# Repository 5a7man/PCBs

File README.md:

# PCBs
## Power Supply

## AVR Based Datalogger

## LED Matrix

## Amplitude Modulation and Demodulation

## Class D Amplifier

## Wireless Power Transmission

## Bluetooth Controlled Vehicle

## Metal Detector

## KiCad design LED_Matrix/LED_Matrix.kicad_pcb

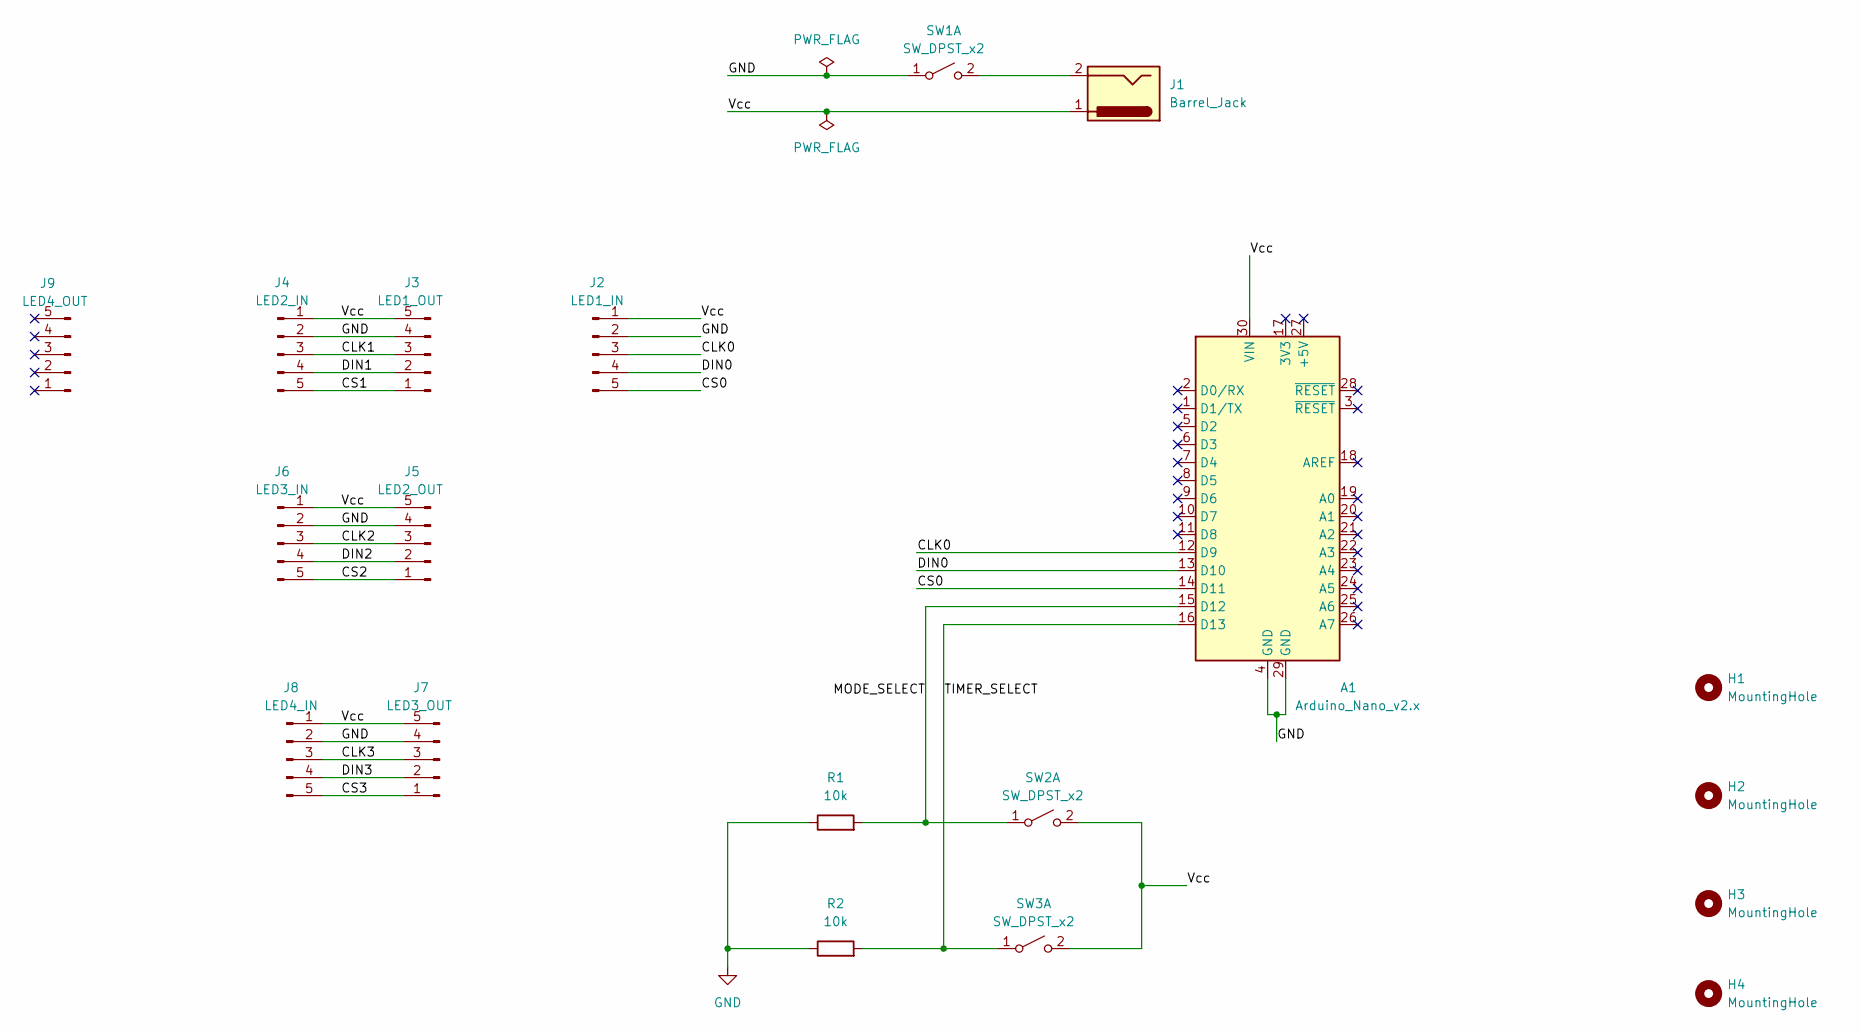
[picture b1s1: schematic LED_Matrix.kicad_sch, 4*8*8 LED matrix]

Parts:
A1: Arduino_Nano_v2.x; Arduino_Nano_WithMountingHoles
H1, H2, H3, H4: MountingHole; MountingHole_2.5mm
J1: Barrel_Jack; BarrelJack_SwitchcraftConxall_RAPC10U_Horizontal
J2: LED1_IN; PinSocket_1x05_P2.54mm_Vertical
J3: LED1_OUT; PinSocket_1x05_P2.54mm_Vertical
J4: LED2_IN; PinSocket_1x05_P2.54mm_Vertical
J5: LED2_OUT; PinSocket_1x05_P2.54mm_Vertical
J6: LED3_IN; PinSocket_1x05_P2.54mm_Vertical
J7: LED3_OUT; PinSocket_1x05_P2.54mm_Vertical
J8: LED4_IN; PinSocket_1x05_P2.54mm_Vertical
J9: LED4_OUT; PinSocket_1x05_P2.54mm_Vertical
R1, R2: 10k; R_Axial_DIN0207_L6.3mm_D2.5mm_P10.16mm_Horizontal
SW1: SW_DPST_x2; SW_DIP_SPSTx02_Slide_6.7x6.64mm_W7.62mm_P2.54mm_LowProfile
SW2, SW3: SW_DPST_x2; Push_E-Switch_KS01Q01

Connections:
/CLK0: A1.12 (D9), J2.3
/CLK1: J3.3, J4.3
/CLK2: J5.3, J6.3
/CLK3: J7.3, J8.3
/CS0: A1.14 (D11), J2.5
/CS1: J3.1, J4.5
/CS2: J5.1, J6.5
/CS3: J7.1, J8.5
/DIN0: A1.13 (D10), J2.4
/DIN1: J3.2, J4.4
/DIN2: J5.2, J6.4
/DIN3: J7.2, J8.4
/MODE_SELECT: A1.15 (D12), R1.2, SW2.1 (A)
/TIMER_SELECT: A1.16 (D13), R2.2, SW3.1 (A)
/Vcc: A1.30 (VIN), J1.1, J2.1, J3.5, J4.1, J5.5, J6.1, J7.5, J8.1, SW2.2 (B), SW3.2 (B)
GND: A1.4 (GND), A1.29 (GND), J2.2, J3.4, J4.2, J5.4, J6.2, J7.4, J8.2, R1.1, R2.1, SW1.1 (A)
unnamed: J1.2, SW1.2 (B)

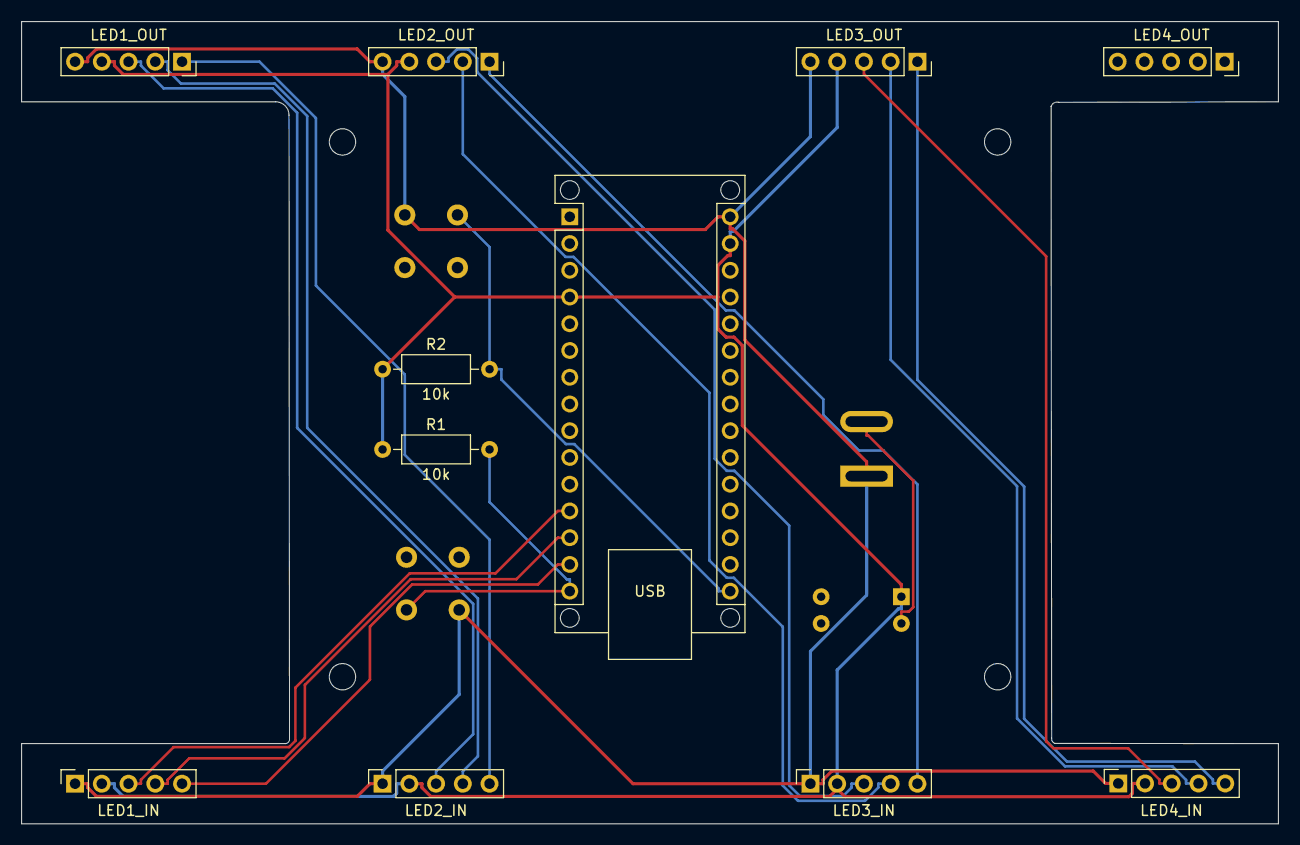
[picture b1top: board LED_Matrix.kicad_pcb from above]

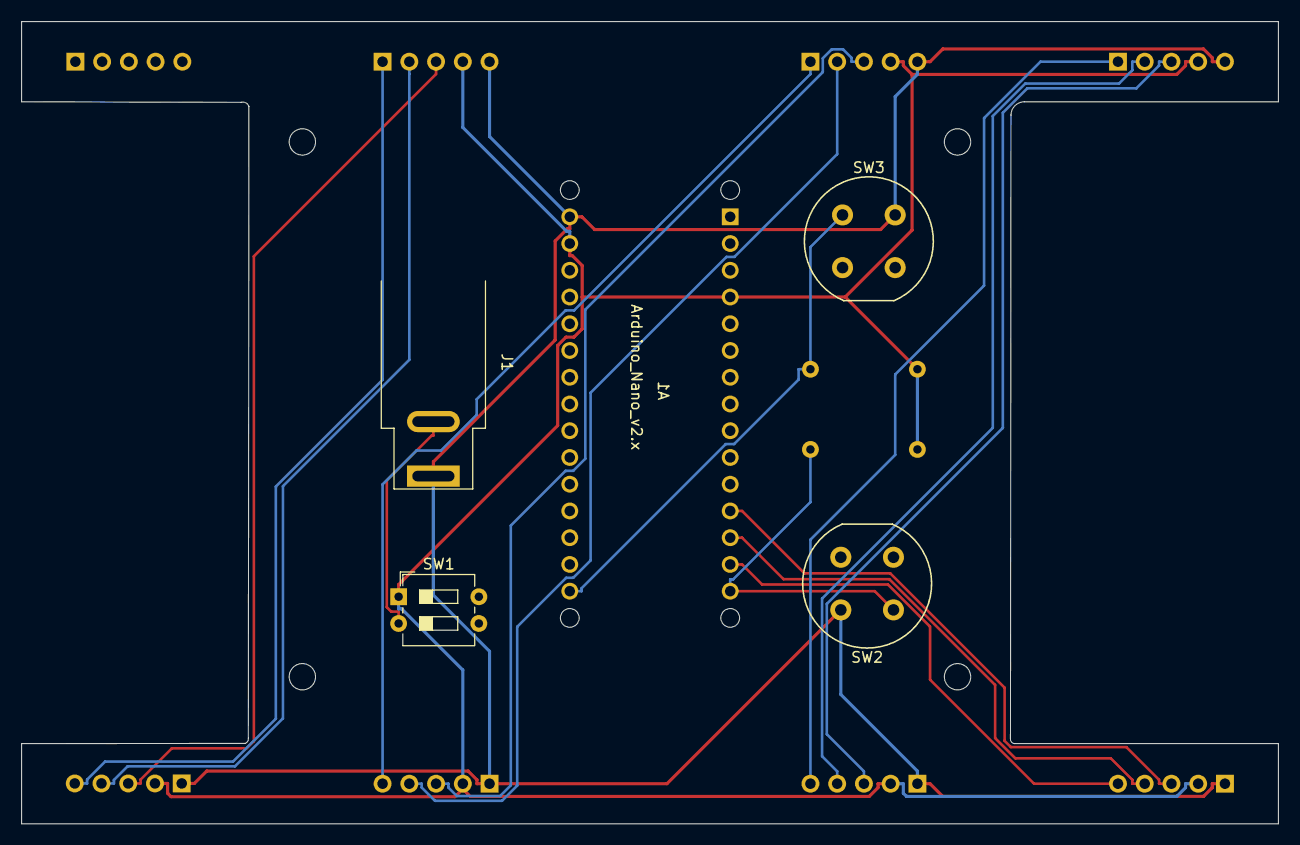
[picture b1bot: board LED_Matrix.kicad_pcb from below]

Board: 2 copper layers, 119.4 x 76.2 mm, 19 parts (4 on the bottom side), 17 nets.

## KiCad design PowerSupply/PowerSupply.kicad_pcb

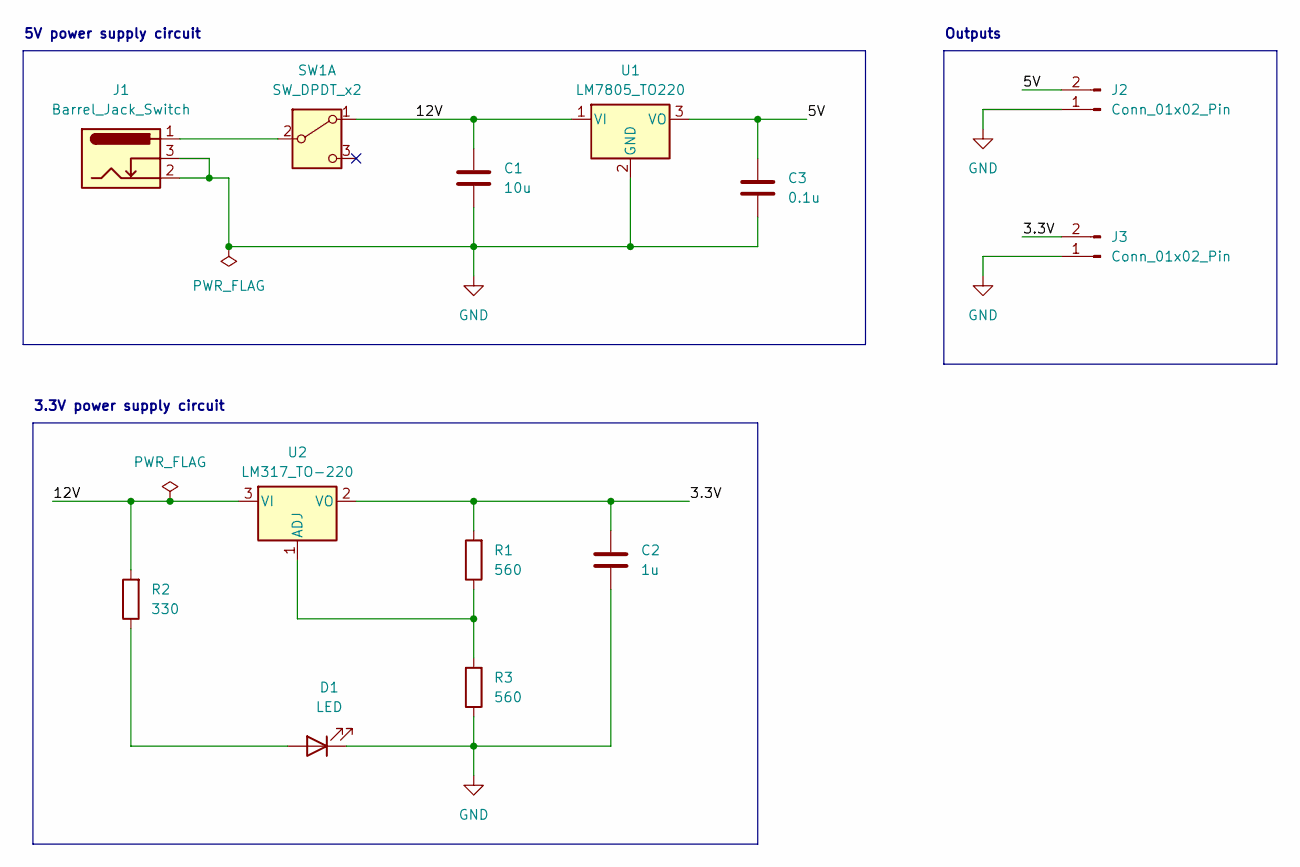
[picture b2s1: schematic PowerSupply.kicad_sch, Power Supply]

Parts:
C1: 10u; C_Disc_D3.0mm_W1.6mm_P2.50mm
C2: 1u; C_Disc_D3.0mm_W1.6mm_P2.50mm
C3: 0.1u; C_Disc_D3.0mm_W1.6mm_P2.50mm
D1: LED; LED_D5.0mm
J1: Barrel_Jack_Switch; BarrelJack_Horizontal
J2, J3: Conn_01x02_Pin; PinHeader_1x02_P2.54mm_Vertical
R1, R3: 560; R_Axial_DIN0204_L3.6mm_D1.6mm_P7.62mm_Horizontal
R2: 330; R_Axial_DIN0204_L3.6mm_D1.6mm_P7.62mm_Horizontal
SW1: SW_DPDT_x2; SW_CuK_JS202011CQN_DPDT_Straight
U1: LM7805_TO220; TO-220-3_Vertical
U2: LM317_TO-220; TO-220-3_Vertical

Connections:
/3.3V: C2.1, J3.2, R1.2, U2.2 (VO)
/5V: C3.1, J2.2, U1.3 (VO)
/12V: C1.1, R2.2, SW1.1 (A), U1.1 (VI), U2.3 (VI)
GND: C1.2, C2.2, C3.2, D1.1 (K), J1.2, J1.3, J2.1, J3.1, R3.1, U1.2 (GND)
unnamed: D1.2 (A), R2.1
unnamed: J1.1, SW1.2 (B)
unnamed: R1.1, R3.2, U2.1 (ADJ)

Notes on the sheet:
Outputs
5V power supply circuit
3.3V power supply circuit

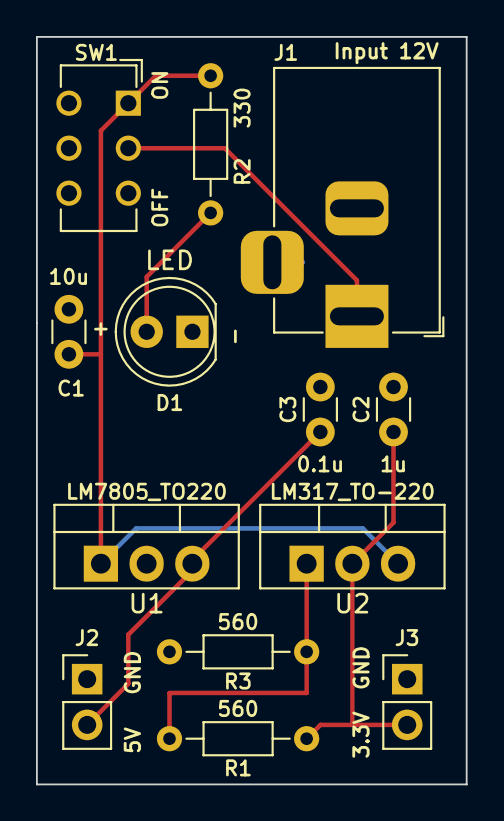
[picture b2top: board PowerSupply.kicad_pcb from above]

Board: 2 copper layers, 23.9 x 41.5 mm, 13 parts (0 on the bottom side), 7 nets.

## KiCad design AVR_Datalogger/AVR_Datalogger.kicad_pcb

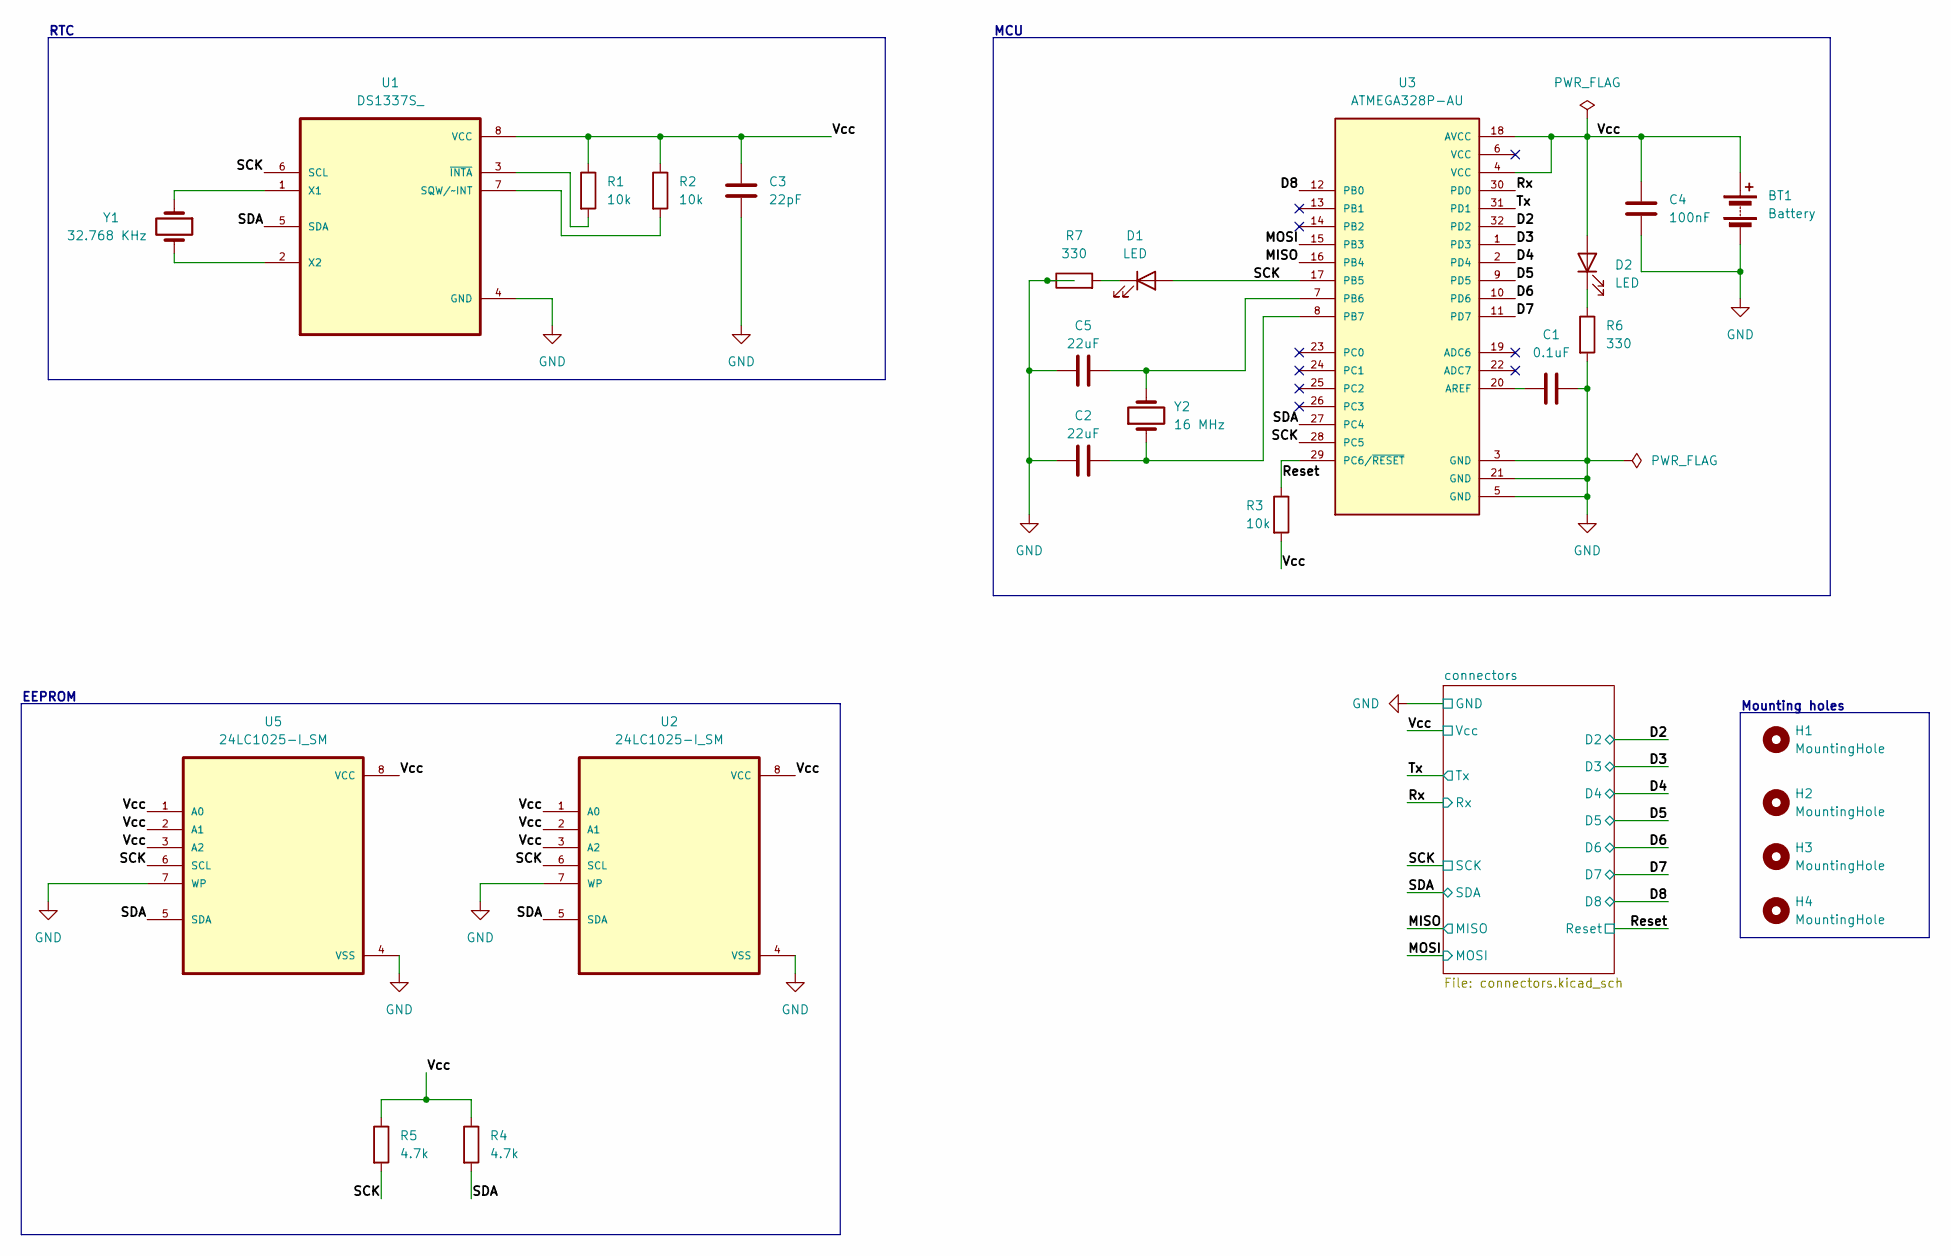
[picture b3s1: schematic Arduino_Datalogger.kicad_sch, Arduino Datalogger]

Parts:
BT1: Battery; PinHeader_1x02_P2.54mm_Vertical
C1: 0.1uF; C_0805_2012Metric
C2, C5: 22uF; C_0805_2012Metric
C3: 22pF; C_0805_2012Metric
C4: 100nF; C_0805_2012Metric
D1, D2: LED; LED_0805_2012Metric
H1, H2, H3, H4: MountingHole; MountingHole_2.1mm
R1, R2, R3: 10k; R_0805_2012Metric
R4, R5: 4.7k; R_0805_2012Metric
R6, R7: 330; R_0805_2012Metric
U1: DS1337S_; SOIC127P600X175-8N
U2, U5: 24LC1025-I_SM; SOIC127P794X202-8N
U3: ATMEGA328P-AU; QFP80P900X900X120-32N; PARTREV 8271A
Y1: 32.768 KHz; Crystal_SMD_5032-2Pin_5.0x3.2mm_HandSoldering
Y2: 16 MHz; Crystal_SMD_5032-2Pin_5.0x3.2mm_HandSoldering

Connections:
/D2: U3.32 (PD2); also elsewhere on the board
/D3: U3.1 (PD3); also elsewhere on the board
/D4: U3.2 (PD4); also elsewhere on the board
/D5: U3.9 (PD5); also elsewhere on the board
/D6: U3.10 (PD6); also elsewhere on the board
/D7: U3.11 (PD7); also elsewhere on the board
/D8: U3.12 (PB0); also elsewhere on the board
/MISO: U3.16 (PB4); also elsewhere on the board
/MOSI: U3.15 (PB3); also elsewhere on the board
/Reset: R3.1, U3.29 (PC6/~RESET); also elsewhere on the board
/Rx: U3.30 (PD0); also elsewhere on the board
/SCK: D1.2 (A), R5.2, U1.6 (SCL), U2.6 (SCL), U3.17 (PB5), U3.28 (PC5), U5.6 (SCL); also elsewhere on the board
/SDA: R4.2, U1.5 (SDA), U2.5 (SDA), U3.27 (PC4), U5.5 (SDA); also elsewhere on the board
/Tx: U3.31 (PD1); also elsewhere on the board
/Vcc: BT1.1 (+), C3.1, C4.1, D2.2 (A), R1.1, R2.1, R3.2, R4.1, R5.1, U1.8 (VCC), U2.1 (A0), U2.2 (A1), U2.3 (A2), U2.8 (VCC), U3.4 (VCC), U3.18 (AVCC), U5.1 (A0), U5.2 (A1), U5.3 (A2), U5.8 (VCC); also elsewhere on the board
GND: BT1.2 (-), C1.2, C2.1, C3.2, C4.2, C5.1, R6.2, R7.1, U1.4 (GND), U2.4 (VSS), U2.7 (WP), U3.3 (GND), U3.5 (GND), U3.21 (GND), U5.4 (VSS), U5.7 (WP); also elsewhere on the board
unnamed: D1.1 (K), R7.2
unnamed: D2.1 (K), R6.1
unnamed: R2.2, U1.7 (SQW/~INT)
unnamed: U1.1 (X1), Y1.1
unnamed: U1.2 (X2), Y1.2
unnamed: R1.2, U1.3 (~INTA)
unnamed: C1.1, U3.20 (AREF)
unnamed: C5.2, U3.7 (PB6), Y2.2
unnamed: C2.2, U3.8 (PB7), Y2.1

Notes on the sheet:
MCU
EEPROM
RTC
Mounting holes

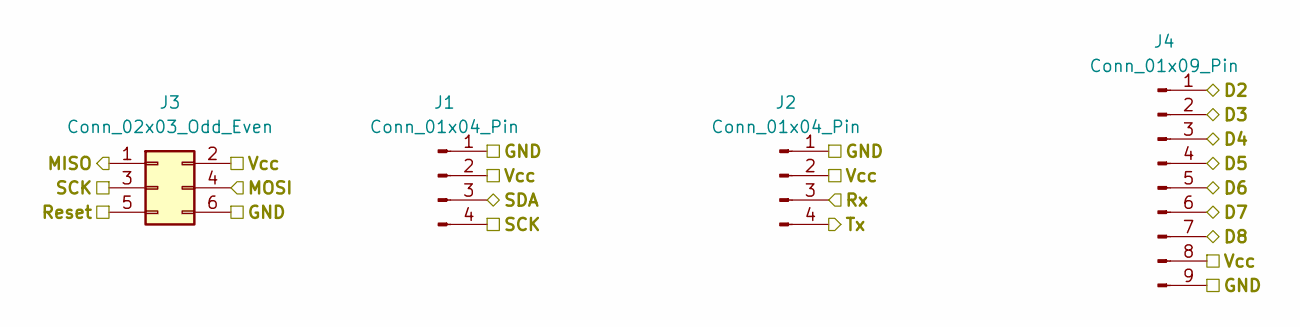
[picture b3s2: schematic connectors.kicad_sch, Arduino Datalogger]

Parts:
J1, J2: Conn_01x04_Pin; PinHeader_1x04_P2.54mm_Vertical
J3: Conn_02x03_Odd_Even; PinSocket_2x03_P2.54mm_Vertical
J4: Conn_01x09_Pin; PinHeader_1x09_P2.54mm_Vertical

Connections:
/D2: J4.1; also elsewhere on the board
/D3: J4.2; also elsewhere on the board
/D4: J4.3; also elsewhere on the board
/D5: J4.4; also elsewhere on the board
/D6: J4.5; also elsewhere on the board
/D7: J4.6; also elsewhere on the board
/D8: J4.7; also elsewhere on the board
/MISO: J3.1; also elsewhere on the board
/MOSI: J3.4; also elsewhere on the board
/Reset: J3.5; also elsewhere on the board
/Rx: J2.3; also elsewhere on the board
/SCK: J1.4, J3.3; also elsewhere on the board
/SDA: J1.3; also elsewhere on the board
/Tx: J2.4; also elsewhere on the board
/Vcc: J1.2, J2.2, J3.2, J4.8; also elsewhere on the board
GND: J1.1, J2.1, J3.6, J4.9; also elsewhere on the board

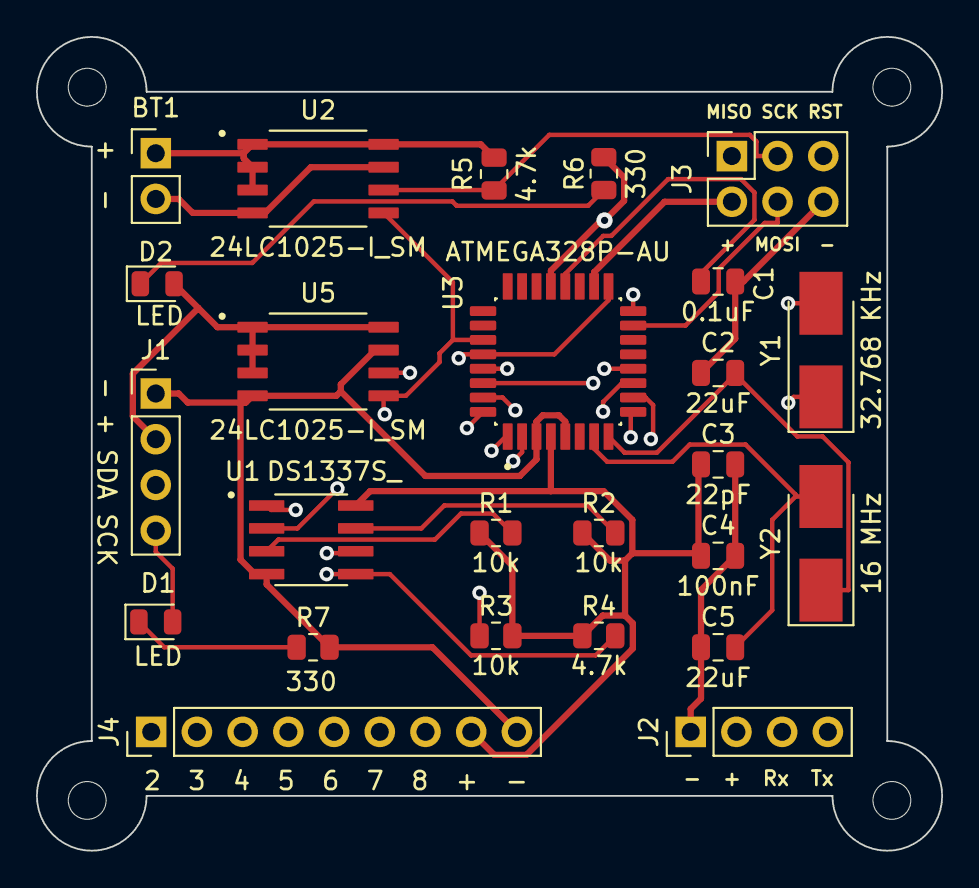
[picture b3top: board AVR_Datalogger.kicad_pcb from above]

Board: 4 copper layers, 50.3 x 45.2 mm, 29 parts (0 on the bottom side), 25 nets.

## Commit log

2024-02-03 added Power Supply
2024-02-06 added copper fills
2024-02-27 Arduino based datalogger
2024-03-01 LED Matrix
2024-06-27 AVR based datalogger
2024-06-27 Amplitude Modulation and Demodulation
2024-06-27 Bluetooth Controlled Vehicle
2024-06-27 Metal Detector
2024-06-27 Class D Amplifier
2024-06-27 Wireless Power Transmission
